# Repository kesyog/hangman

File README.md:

# hangman ⚖️

Hangman is a Bluetooth-enabled crane scale. It's intended use is as a climbing training and rehab
tool, but it can be used anywhere that requires measuring force or weight.

The hardware retrofits a cheap (~$23) 150kg crane scale from Amazon with a custom PCB based around a
Nordic nRF52 microcontroller and a differential ADC. The firmware uses [Embassy][Embassy], an
embedded async framework written in Rust, as well as Nordic's SoftDevice Bluetooth stack.

## Why?

Crane scales have become popular in the climbing community as a means to train and rehab fingers.
This is a fun project to learn and practice various concepts I was unfamiliar or rusty with: BLE
101, async Rust on embedded, nRF52 development, SMT soldering and PCB design, etc. Maybe it'll even
help my fingers get stronger.

## Status

The scale is feature-complete. Weight measurement works great with the [Progressor API][API] and
compatible tools. Battery life is guesstimated to be in the range of several months to a couple of
years depending on usage.

There are still a few more software updates planned. See the Issues section for the major ones.

### Hardware revisions

#### P1.0

See title picture. A custom PCB based on a Fanstel BT832 nRF52832-based module and a Texas
Instruments ADS1230 ADC. Thanks to a better ADC and PCB layout, noise performance should be improved
over previous revisions and most importantly, it's much prettier.

#### P0.0

A custom PCB based on a nRF52840 USB dongle and an HX711 ADC, the same differential ADC used on the
Tindeq.

## Shoutouts

* The [Embassy](https://embassy.dev) project for bringing asynchronous Rust to the embedded world.
  and creating an easy to use wrapper around the Nordic SoftDevice Bluetooth stack.
* [Bumble](https://github.com/google/bumble) for BLE testing and prototyping.
* Texas Instruments for their excellent reference materials on load cell circuit design and PCB
  layout.
* [Tindeq](https://tindeq.com/product/progressor/) for making an amazing product and app and opening
  their BLE API to third-party developers. Go buy one!

## Disclaimer

This is not an officially supported Google product. Wouldn't that be funny though?

This has no affiliation with Tindeq.

[API]: https://tindeq.com/progressor_api/
[Embassy]: https://embassy.dev/

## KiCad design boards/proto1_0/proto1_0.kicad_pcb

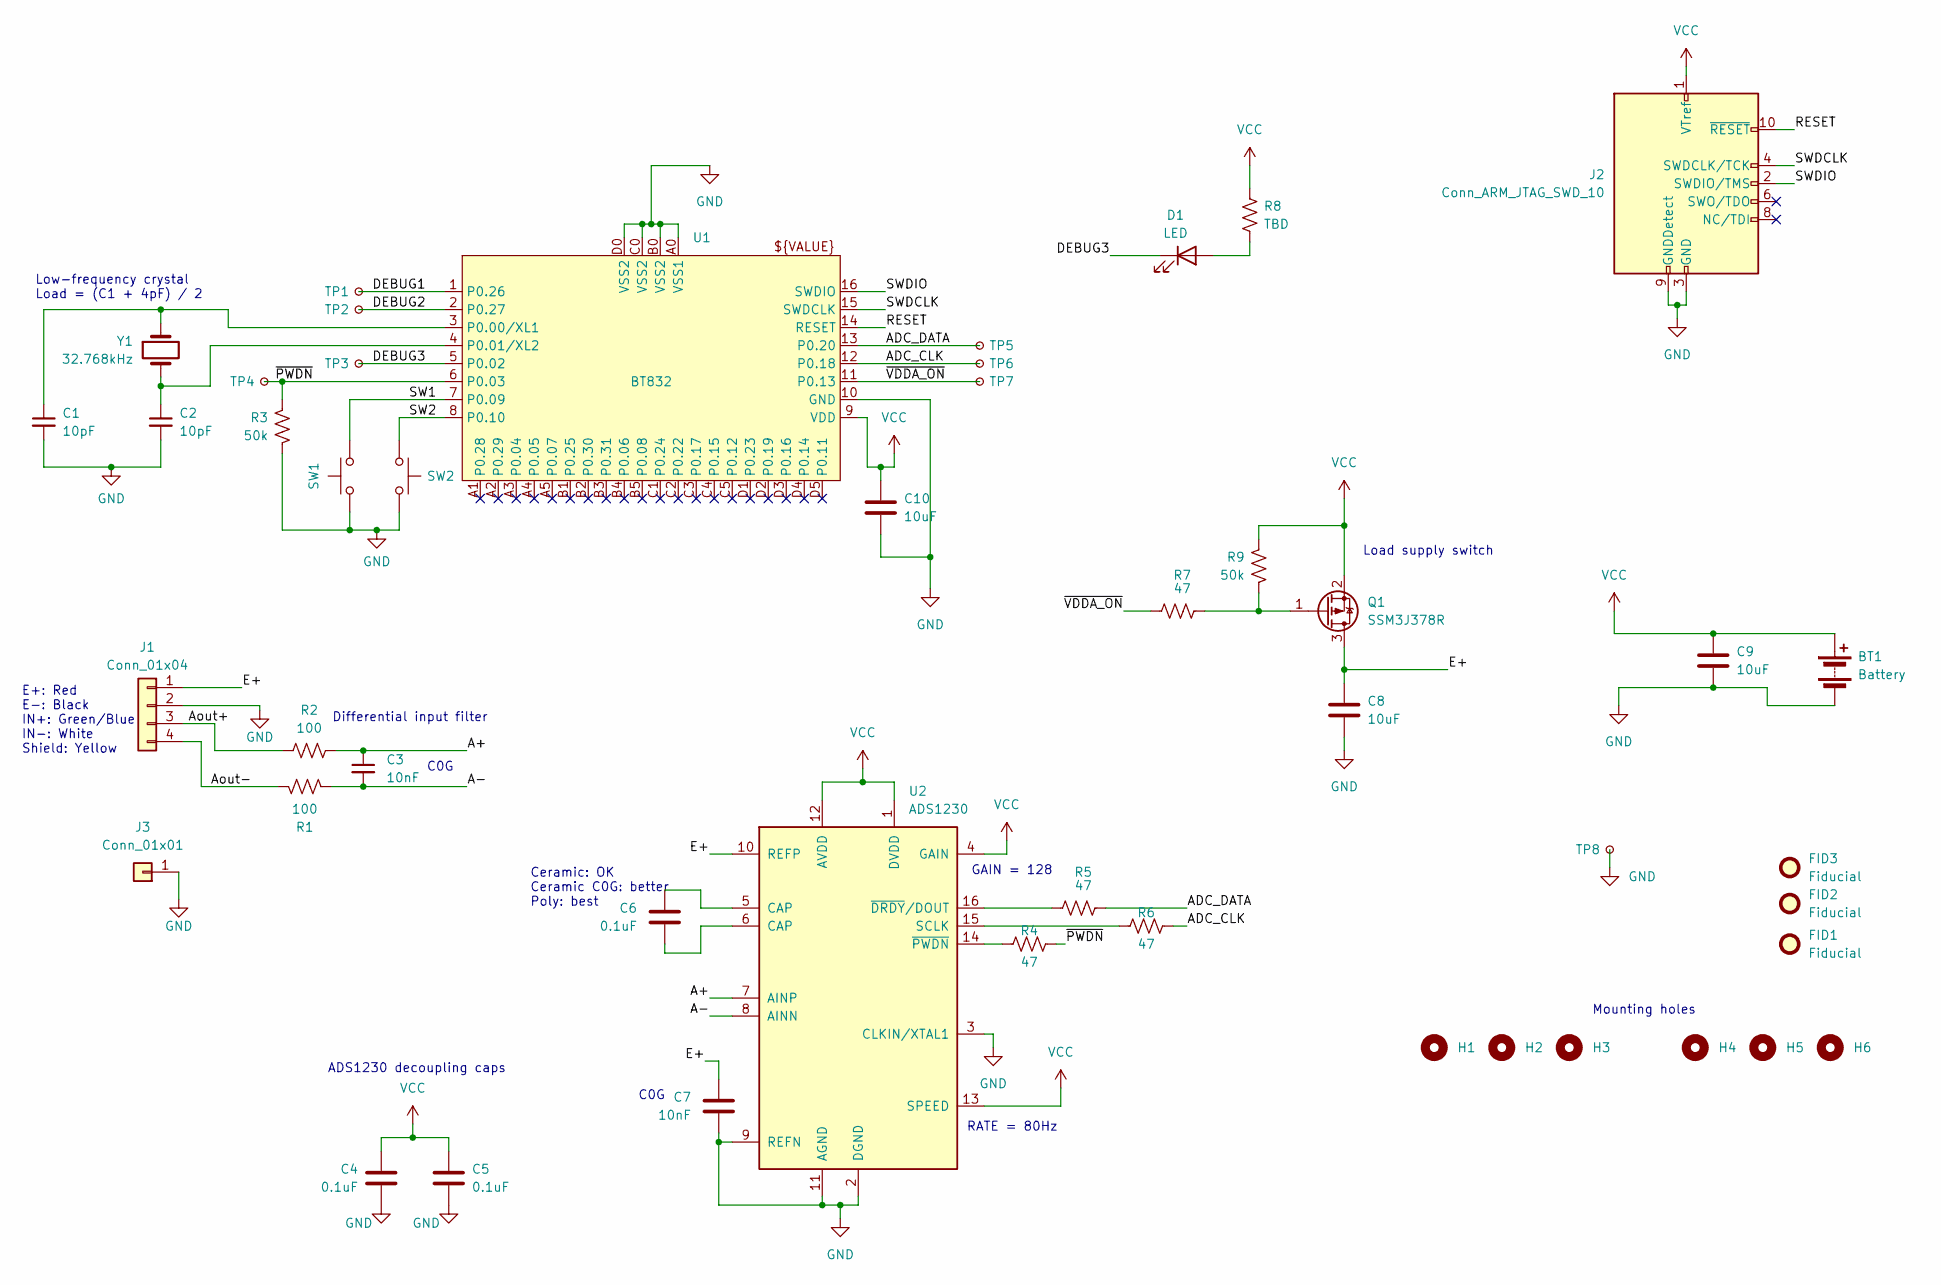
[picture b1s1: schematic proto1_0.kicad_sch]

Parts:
BT1: Battery; SolderWire-0.5sqmm_1x02_P4.6mm_D0.9mm_OD2.1mm
C1, C2: 10pF; C_0603_1608Metric
C3, C7: 10nF; C_0603_1608Metric
C4, C5, C6: 0.1uF; C_0603_1608Metric
C8, C9, C10: 10uF; C_0805_2012Metric
D1: LED; LED_0603_1608Metric_Pad1.05x0.95mm_HandSolder
FID1, FID2, FID3: Fiducial; Fiducial_0.5mm_Mask1mm
H1, H2, H3, H4, H5, H6: MountingHole; MountingHole_2.2mm_M2
J1: Conn_01x04; SolderWire-0.1sqmm_1x04_P3.6mm_D0.4mm_OD1mm
J2: Conn_ARM_JTAG_SWD_10; PinHeader_2x05_P1.27mm_Vertical_SMD
J3: Conn_01x01; SolderWire-0.5sqmm_1x01_D0.9mm_OD2.1mm
Q1: SSM3J378R; SOT-23
R1, R2: 100; R_0603_1608Metric
R3, R9: 50k; R_0603_1608Metric
R4, R5, R6, R7: 47; R_0603_1608Metric
R8: TBD; R_0805_2012Metric
SW1, SW2: 2223-TS02-66-70-BK-160-LCR-D-ND (Digikey); SW_PUSH_6mm_H7.3mm
TP1, TP2, TP3, TP4, TP5, TP6, TP7, TP8: TestPoint_Small; TestPoint_Pad_D1.5mm
U1: BT832
U2: ADS1230; TSSOP-16_4.4x5mm_P0.65mm
Y1: 32.768kHz; Crystal_SMD_3215-2Pin_3.2x1.5mm; Part number SC32S-7PF20PPM

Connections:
/A+: C3.1, R2.2, U2.7 (AINP)
/A-: C3.2, R1.2, U2.8 (AINN)
/ADC_CLK: R6.2, TP6.1, U1.12 (P0.18)
/ADC_DATA: R5.2, TP5.1, U1.13 (P0.20)
/Aout+: J1.3, R2.1
/Aout-: J1.4, R1.1
/DEBUG1: TP1.1, U1.1 (P0.26)
/DEBUG2: TP2.1, U1.2 (P0.27)
/DEBUG3: D1.1 (K), TP3.1, U1.5 (P0.02)
/E+: C7.1, C8.1, J1.1, Q1.3 (D), U2.10 (REFP)
/RESET: J2.10 (~RESET), U1.14 (RESET)
/SW1: SW1.1, U1.7 (P0.09)
/SW2: SW2.1, U1.8 (P0.10)
/SWDCLK: J2.4 (SWDCLK/TCK), U1.15 (SWDCLK)
/SWDIO: J2.2 (SWDIO/TMS), U1.16 (SWDIO)
/~PWDN: R3.1, R4.2, TP4.1, U1.6 (P0.03)
/~VDDA_ON: R7.1, TP7.1, U1.11 (P0.13)
GND: BT1.2 (-), C1.2, C2.2, C4.2, C5.2, C7.2, C8.2, C9.2, C10.2, J1.2, J2.3 (GND), J2.5 (GND), J2.9 (GNDDetect), J3.1, R3.2, SW1.2, SW2.2, TP8.1, U1.10 (GND), U1.A0 (VSS1), U1.B0 (VSS2), U1.C0 (VSS2), U1.D0 (VSS2), U2.2 (DGND), U2.3 (CLKIN/XTAL1), U2.9 (REFN), U2.11 (AGND)
unnamed: C6.1, U2.5 (CAP)
unnamed: C6.2, U2.6 (CAP)
unnamed: D1.2 (A), R8.2
unnamed: Q1.1 (G), R7.2, R9.2
unnamed: C1.1, U1.3 (P0.00/XL1), Y1.1
unnamed: C2.1, U1.4 (P0.01/XL2), Y1.2
unnamed: R6.1, U2.15 (SCLK)
unnamed: R5.1, U2.16 (~DRDY/DOUT)
unnamed: R4.1, U2.14 (~PWDN)
VCC: BT1.1 (+), C4.1, C5.1, C9.1, C10.1, J2.1 (VTref), Q1.2 (S), R8.1, R9.1, U1.9 (VDD), U2.1 (DVDD), U2.4 (GAIN), U2.12 (AVDD), U2.13 (SPEED)

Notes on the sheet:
Load supply switch
E+: Red E-: Black IN+: Green/Blue IN-: White Shield: Yellow
Differential input filter
Low-frequency crystal Load = (C1 + 4pF) / 2
C0G
Mounting holes
RATE = 80Hz
GAIN = 128
Ceramic: OK Ceramic C0G: better Poly: best
ADS1230 decoupling caps

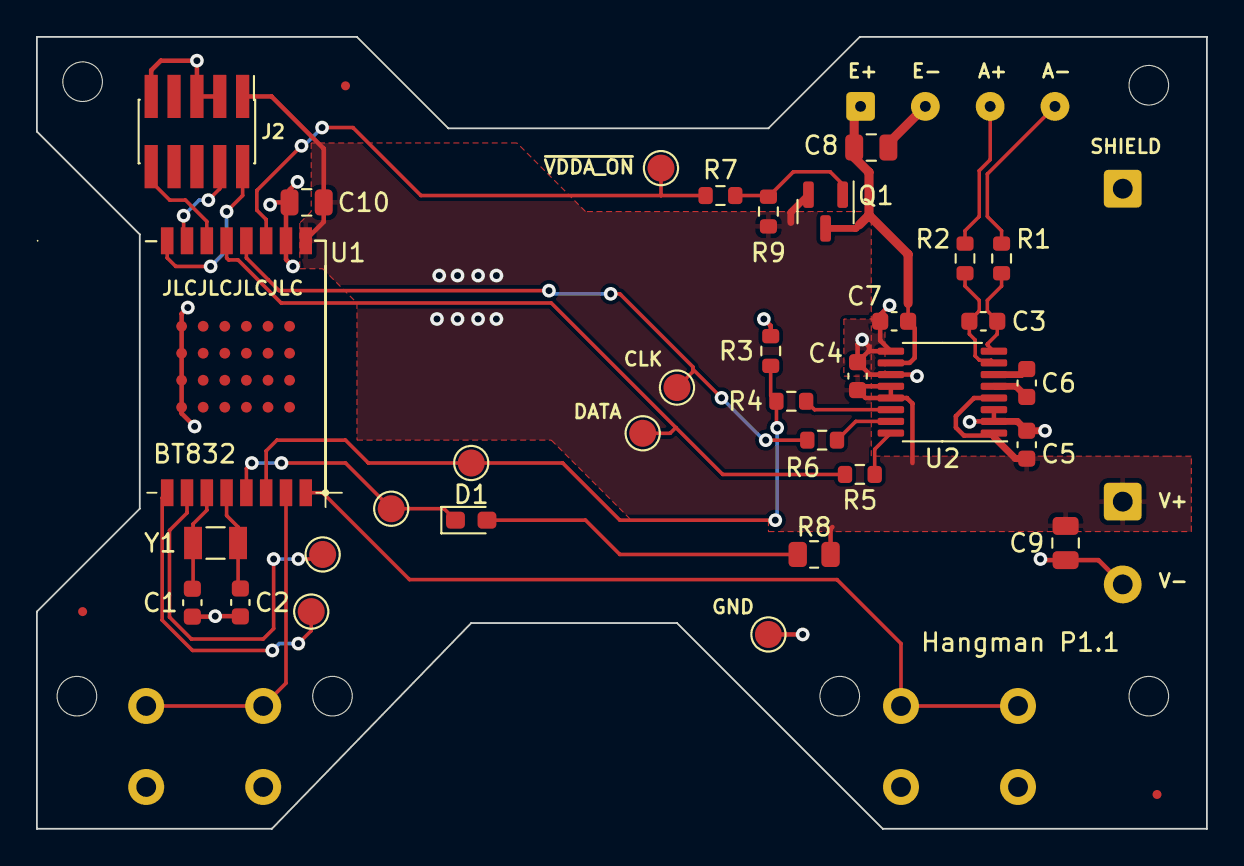
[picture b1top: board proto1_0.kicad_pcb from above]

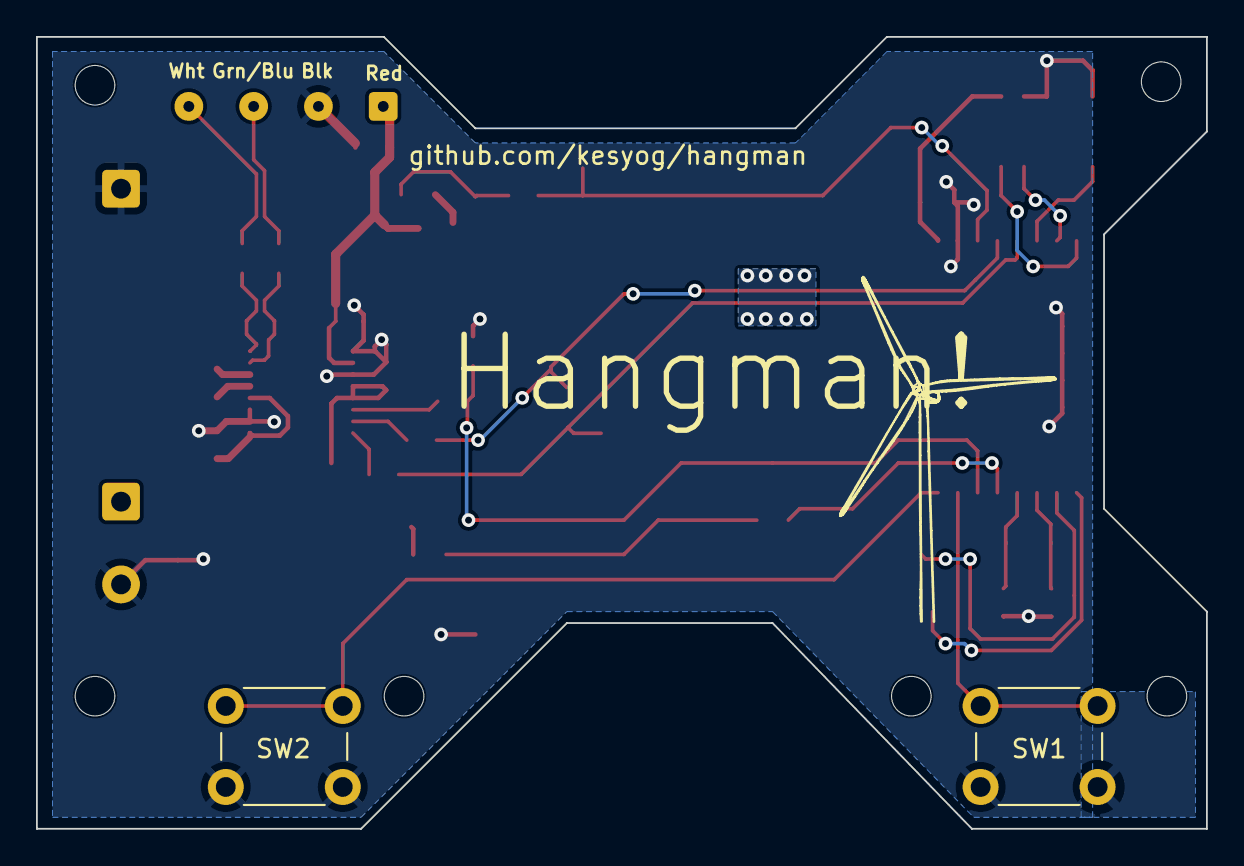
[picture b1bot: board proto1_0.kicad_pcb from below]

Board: 2 copper layers, 65.0 x 44.0 mm, 47 parts (2 on the bottom side), 28 nets.

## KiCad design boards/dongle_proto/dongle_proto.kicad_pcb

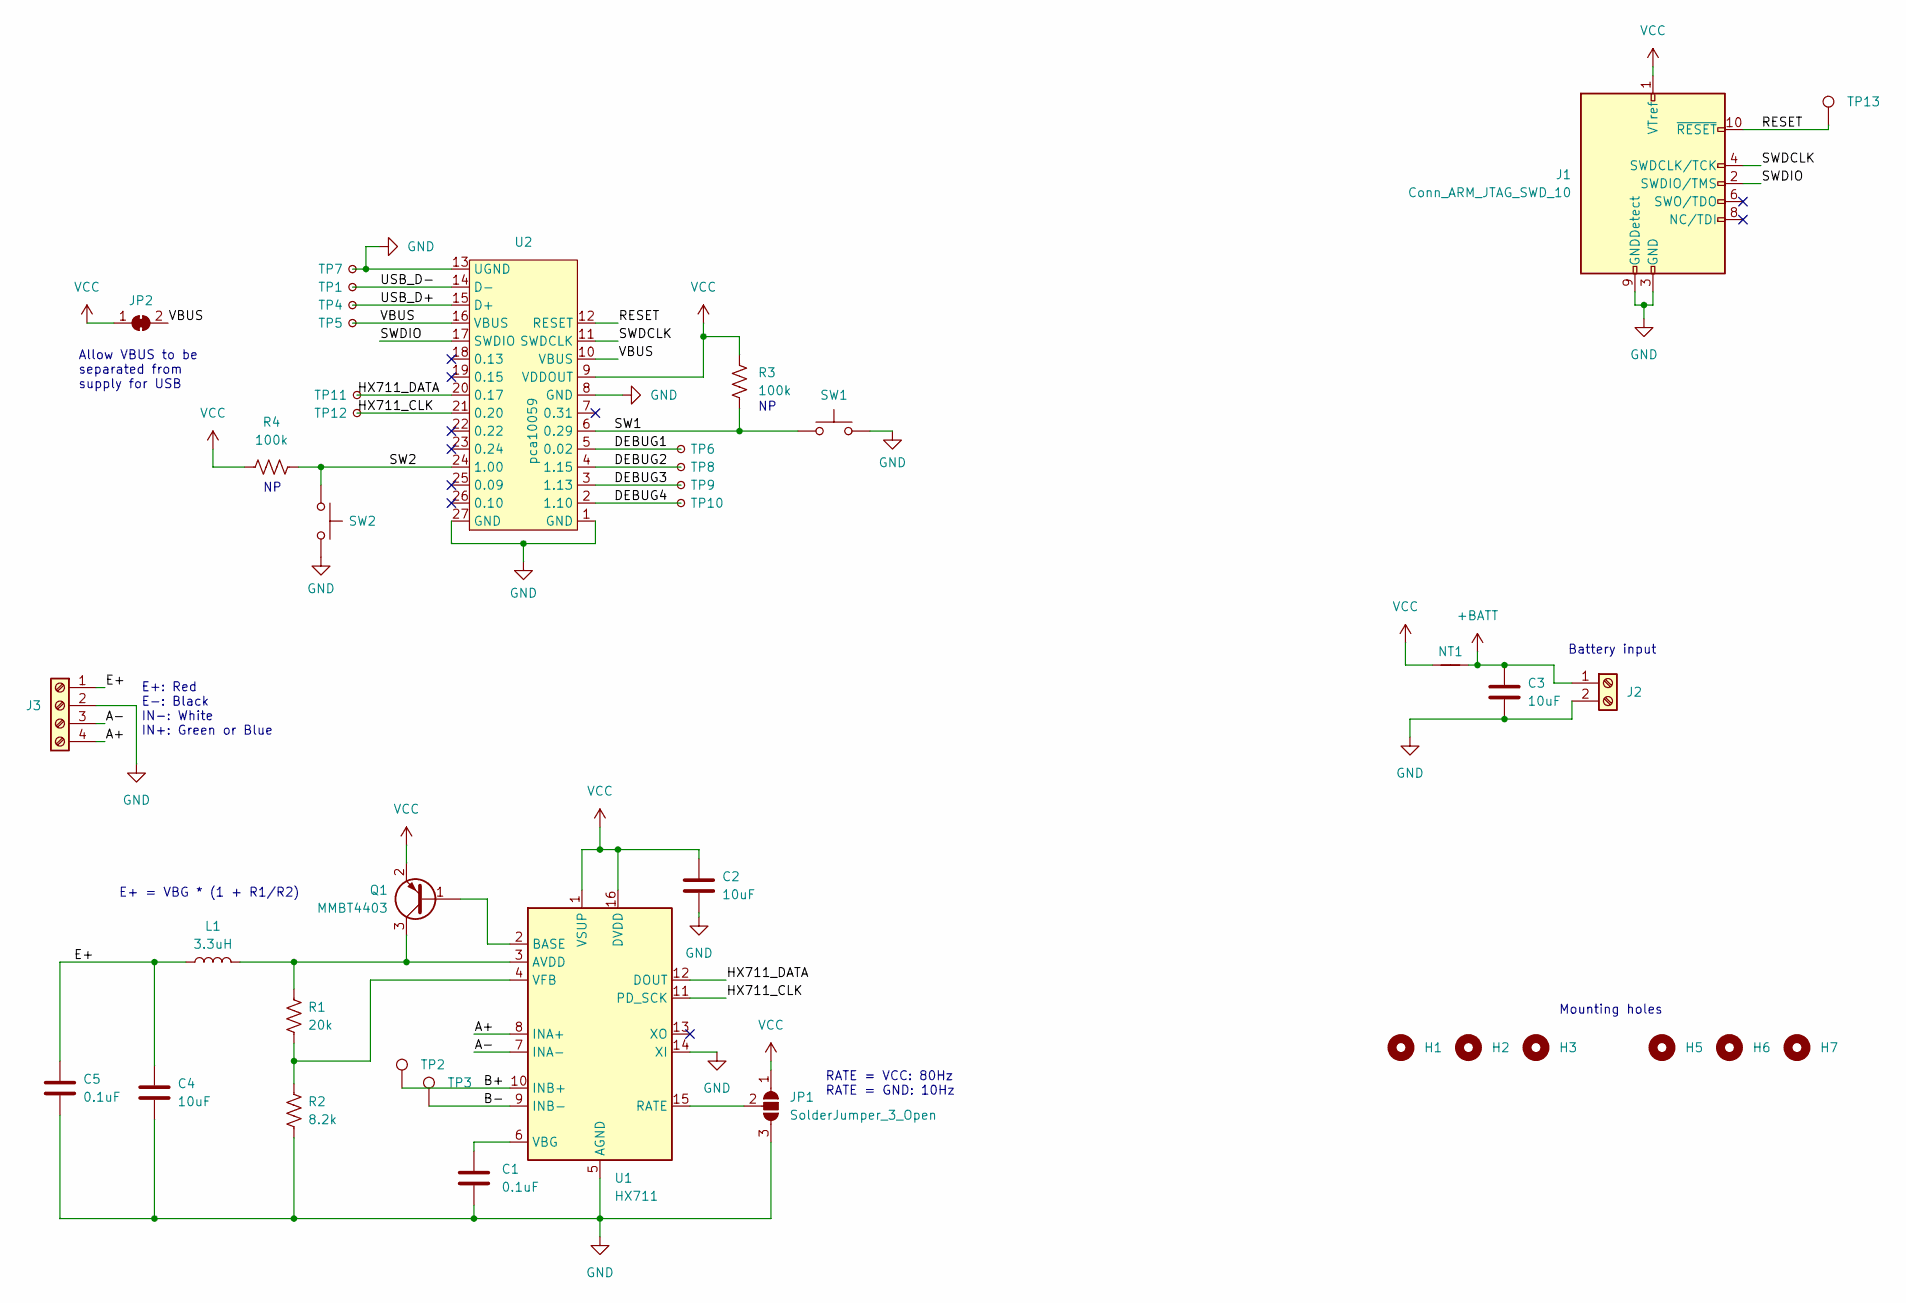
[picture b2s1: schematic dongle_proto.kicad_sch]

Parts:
C1, C5: 0.1uF; C_0805_2012Metric_Pad1.18x1.45mm_HandSolder
C2, C3, C4: 10uF; C_0805_2012Metric_Pad1.18x1.45mm_HandSolder
H1, H2, H3, H5, H6, H7: MountingHole; MountingHole_2.2mm_M2
J1: Conn_ARM_JTAG_SWD_10; PinHeader_2x05_P1.27mm_Vertical_SMD
J2: Screw_Terminal_01x02; TerminalBlock_Phoenix_MPT-0,5-2-2.54_1x02_P2.54mm_Horizontal
J3: Screw_Terminal_01x04; TerminalBlock_Phoenix_MPT-0,5-4-2.54_1x04_P2.54mm_Horizontal
JP1: SolderJumper_3_Open; SolderJumper-3_P1.3mm_Open_RoundedPad1.0x1.5mm
JP2: SolderJumper_2_Bridged; SolderJumper-2_P1.3mm_Bridged_RoundedPad1.0x1.5mm
L1: 3.3uH; L_0805_2012Metric_Pad1.05x1.20mm_HandSolder
NT1: NetTie_2; NetTie-2_SMD_Pad2.0mm
Q1: MMBT4403; SOT-23_Handsoldering
R1: 20k; R_0805_2012Metric_Pad1.20x1.40mm_HandSolder
R2: 8.2k; R_0805_2012Metric_Pad1.20x1.40mm_HandSolder
R3, R4: 100k; R_0805_2012Metric_Pad1.20x1.40mm_HandSolder
SW1, SW2: 2223-TS02-66-70-BK-160-LCR-D-ND (Digikey); SW_PUSH_6mm_H7.3mm
TP1, TP4, TP5, TP6, TP7, TP8, TP9, TP10, TP11, TP12: TestPoint_Small; TestPoint_Pad_D1.5mm
TP2, TP3, TP13: TestPoint; TestPoint_Pad_D1.5mm
U1: HX711; SOP-16_3.9x9.9mm_P1.27mm
U2: pca10059

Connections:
+BATT: C3.1, J2.1, NT1.2
/A+: J3.4, U1.8 (INA+)
/A-: J3.3, U1.7 (INA-)
/B+: TP2.1, U1.10 (INB+)
/B-: TP3.1, U1.9 (INB-)
/DEBUG1: TP6.1, U2.5 (0.02)
/DEBUG2: TP8.1, U2.4 (1.15)
/DEBUG3: TP9.1, U2.3 (1.13)
/DEBUG4: TP10.1, U2.2 (1.10)
/E+: C4.1, C5.1, J3.1, L1.1
/HX711_CLK: TP12.1, U1.11 (PD_SCK), U2.21 (0.20)
/HX711_DATA: TP11.1, U1.12 (DOUT), U2.20 (0.17)
/RESET: J1.10 (~RESET), TP13.1, U2.12 (RESET)
/SW1: R3.2, SW1.1, U2.6 (0.29)
/SW2: R4.2, SW2.1, U2.24 (1.00)
/SWDCLK: J1.4 (SWDCLK/TCK), U2.11 (SWDCLK)
/SWDIO: J1.2 (SWDIO/TMS), U2.17 (SWDIO)
/USB_D+: TP4.1, U2.15 (D+)
/USB_D-: TP1.1, U2.14 (D-)
/VBUS: JP2.2 (B), TP5.1, U2.10 (VBUS), U2.16 (VBUS)
GND: C1.2, C2.2, C3.2, C4.2, C5.2, J1.3 (GND), J1.5 (GND), J1.9 (GNDDetect), J2.2, J3.2, JP1.3 (B), R2.2, SW1.2, SW2.2, TP7.1, U1.5 (AGND), U1.14 (XI), U2.1 (GND), U2.8 (GND), U2.13 (UGND), U2.27 (GND)
unnamed: JP1.2 (C), U1.15 (RATE)
unnamed: Q1.1 (B), U1.2 (BASE)
unnamed: L1.2, Q1.3 (C), R1.1, U1.3 (AVDD)
unnamed: C1.1, U1.6 (VBG)
unnamed: R1.2, R2.1, U1.4 (VFB)
VCC: C2.1, J1.1 (VTref), JP1.1 (A), JP2.1 (A), NT1.1, Q1.2 (E), R3.1, R4.1, U1.1 (VSUP), U1.16 (DVDD), U2.9 (VDDOUT)

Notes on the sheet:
Battery input
E+: Red E-: Black IN-: White IN+: Green or Blue
Mounting holes
E+ = VBG * (1 + R1/R2)
Allow VBUS to be separated from supply for USB
RATE = VCC: 80Hz RATE = GND: 10Hz

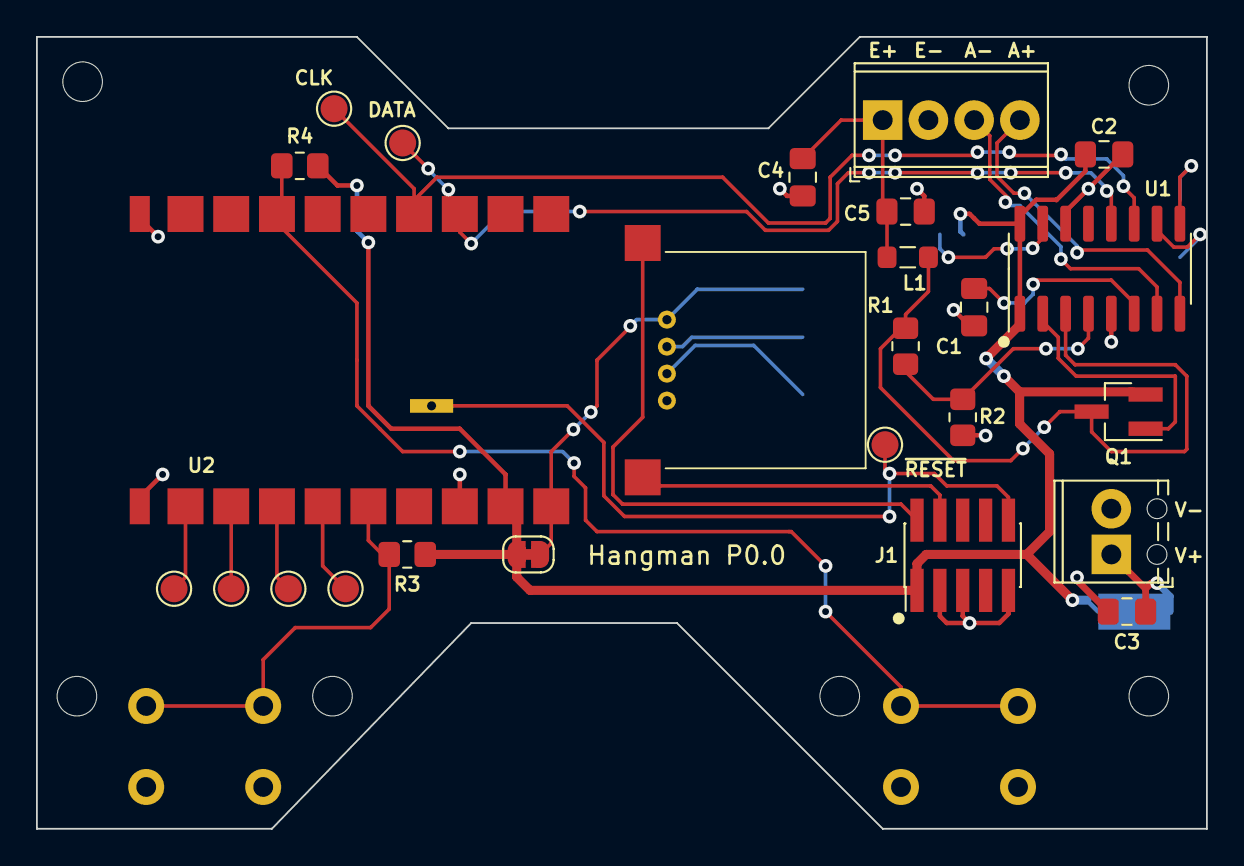
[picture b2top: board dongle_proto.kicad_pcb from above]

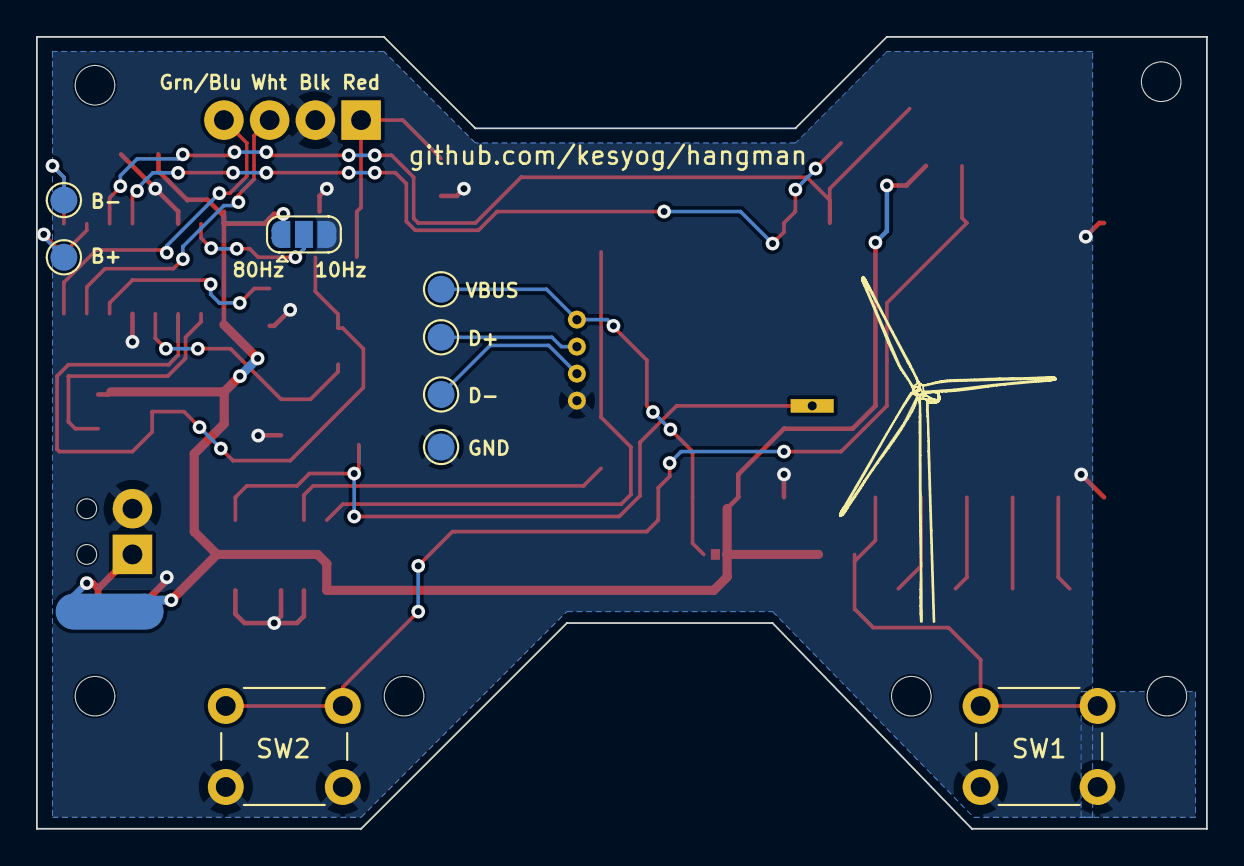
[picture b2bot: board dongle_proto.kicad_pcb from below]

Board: 2 copper layers, 65.0 x 44.0 mm, 40 parts (10 on the bottom side), 27 nets.

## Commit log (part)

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2023-02-05 Working blinky on nRF52840 dongle
2023-02-05 Switch to Embassy executor and HAL
    Using the async Embassy framework will be required to use the
    `nrf-softdevice` crate, which we'll likely later use to access the
    SoftDevice.
2023-02-05 Use nrfutil to load FW via the Nordic bootloader
    Nordic's GUI programming tool doesn't work well with the bootloader
2023-02-11 Add CDC-ACM USB class with echo
2023-02-11 Add logging over RTT
    * Add support for defmt logging over RTT
    * Switch cargo runner to probe-run, which supports defmt parsing
2023-02-11 Start the SoftDevice
2023-02-20 Add measurement task with fake data
2023-02-26 Add small heap for passing around closures
2023-02-26 Add NVM driver to store calibration constants
    Bonus: lower most `println` logs to lower priorities
2023-02-26 Hook up HX711 driver to GATT commands
    * Add bit-banged HX711 driver
    * Add some default calibration constants
    * Show status with LED's
    * Reduce RAM section size to simulate smallest nRF52 chip
    It works with the Tindeq app!
2023-02-27 Remove measurement -> gatt notify dependency via callback
2023-07-15 Fix breaking changes in dependencies
    embassy made a lot of breaking changes in their git repo. Their API's
    are not stable and the dependency is not pinned to any specific git
    commit.
    Fix up the breaking changes and update all dependencies while we're at
    it.
2023-07-15 Add additional control event opcodes
    Add definitions and parsing of additional undocumented control point
    opcodes. For now, these opcodes are logged but otherwise ignored.
2023-07-16 Make reported sample timestamps more accurate
    Treat the moment that the HX711 reports a sample is ready as the sample
    time. We were previously reading a timestamp after the sample had been
    shifted out to the processor, which introduces a relatively fixed offset
    that shouldn't matter in practice, but accuracy is accuracy.
2023-07-25 🤞🏽 Add Kicad files for P0.0 prototype board
    Add schematic, symbol library, footprint library, and layout for P0.0
    prototype board.
2023-07-29 Simplify/complicate window averager via generics
2023-07-29 🧹 Refactor weight sampling code
    Goals:
    * Make it easier to add new functionality, especially filtering (for
    calibration and taring) and a calibration flow.
    * Clean up a lot of cruft that made things extra hard to follow and
    edit.
    Changes:
2023-07-29 Fix crash in Flash driver
    Flash transactions must only be performed with 4-byte aligned buffers
2023-07-29 Simplify NVM API and remove strum dependency
2023-07-29 Disable USB by default
    * Move as much USB code out of main.rs as possible.
    * Gate USB and echo task on the "console" feature, which is disabled by
    default.
2023-07-29 Reduce logging level of individual measurements
2023-08-04 Use window filter when taring scale
2023-08-17 Fix HX711 AVDD level
    The HX711's analog output (AVDD) should be set below its supply voltage
    (the battery voltage) so that the chip's feedback loop can create a
    stable excitation voltage that is resilient to load transients. The
    R1/R2 resistor ladder was set such that AVDD would always rail to the
    supply voltage. Set it to ~2.7-2.8V instead.
    Note: it's possible that this doesn't actually matter since the ADC
2023-08-17 Reduce sample noise + miscellaneous cleanup
    * Add 5-point median filter in sample pipeline to filter glitches in
    samples
    * Use `make_static!` convenience macro to initialize `StaticCell`s
    * Disable LED's to save power
    * Store window size in window average rather than using const generics
    to reduce monomorphization code bloat.
2023-08-20 Fix Clippy lints
2023-08-21 Create separate binary for manual calibration
    Stuffing everything into one binary was becoming increasingly painful.
    Create a lib crate and separate binaries for the main scale code and the
    manual calibration code.
    Eventually, we'll likely want separate binaries for each board variant
    and and to think harder about how to move common code into the lib
    crate. Ideally, the code in the binaries will be entirely
2023-08-21 Return dummy responses to speed up connection
    The Tindeq app queries a few parameters on connection and also when the
    settings page is opened in the app:
    * Versino number
    * Battery voltage
    * Progressor ID (undocumented query with opcode 0x70)
    These requests were being ignored. Although the app eventually gives up
2023-08-25 Enter system OFF between BLE connections to save power
    * Enter system OFF after advertising timeouts or disconnects, using the
    wakeup button as the wakeup trigger.
    * Minor cleanup: centralize the definition of the `blocking_hal` and pac
    crates to make it easier to switch to other nRF52 parts in the future.
2023-08-26 Enable DC-DC converter for power savings
    The MCU should automatically switch between the DC-DC converter and the
    LDO to optimize conversion efficiency. Didn't actually measure power
    with and without this change but it _should_ work 😬
2023-08-26 Inject sampling frequency from binary
    The dongle development setup is configured with a 10Hz sampling
    frequency, whereas everything else uses 80Hz. Allow this parameter to be
    injected into the weight task rather than hard-coding it.
    The sampling frequency is primarily used for configuring the taring
    process. Accidentally using the default 80Hz value with the dongle
    results in very slow startup.
2023-08-26 Reduce SoftDevice RAM usage via easy-mode tuning
    * Reduce SoftDevice RAM memory usage from ~15kB to ~8kB, knowing that we
    only support one connection at a time and should only need a small
    MTU. This gives even more headroom to use smaller nRF52 devices, if
    desired, which only have 24kB of RAM.
    * Allow 2M secondary Phy. This might save some marginal power by running
    the radio less.
2023-08-29 Add proto1_0 board
    Add schematic and PCB for another prototype board, P1.0.
    Main changes from the first prototype PCB (P0.0):
    * Based on TI ADS1230 ADC IC rather than HX711
    * More thoughtful layout of ADC
    * Using Fanstel BT832 module rather than a Nordic USB dongle
    This will require some software changes to get working in a future
2023-09-10 Fix bad transistor pin assignment
    The load cell power switch (Q1) used a PFET symbol that incorrectly
    numbered its pins relative to the industry-standard for SOT-23 packages.
    Use a more accurate symbol instead and fix the layout accordingly.
    While a P1.1 board is not (yet) planned since this issue should be easy
    to work around,, I've kept the footprint locations the same so that the
    P1.0 stencil can be reused.
2023-09-25 Support runtime calibration via Bluetooth
    Add two-point calibration over Bluetooth. To simplify the math required,
    one of the points must be zero.
    The routine uses documented calibration opcodes but uses its own payload
    format:
    Add calibration point:
    Opcode: 0x69
2023-09-25 Ensure checksum write to flash is aligned
    Writes to flash must originate from 4-byte buffers. This wasn't being
    enforced, so we were getting lucky.
2023-09-25 Fix flipped PCB silkscreen
    The white and green color labels for the load cell differential output
    voltage pins were switched. There's no real functional effect since the
    negative polarity would be fixed in calibration, but one can swap the
    wires if desired.
2023-09-25 Add support for Proto 1.0 board
    * Add mutually-exclusive feature flags for nRF52832 and nRF52840. This
    abuses the feature flag system, but that's embedded life for you.
    Embassy also uses this pattern.
    * Add ADS1230 driver
    * Add blinky, calibration, and application binaries for Proto 1.0
    Note: Some library code abuses the nRF52832 vs. nRF52840 feature flags
2023-09-25 Add missing license headers
2023-10-01 Enable excitation voltage only when needed 🔋
    Save some power by only enabling the load cell excitation voltage when
    actively measuring. This should save (~10-35mW) when Hangman is awake
    but not actively measuring.
2023-10-01 Sample battery voltage at startup
    * Sample battery voltage at startup
    * Shut down immediately if critically low (<= 2.7V)
    * Report low battery warning and disconnect from connected peer if
    battery is just low (<= 2.75V)
2023-10-01 Cleanup some Clippy lints and add documentation
    Also add some basic state checking to weight command handler
2023-10-01 Reduce BLE transmit power from 0dB to -4dB
    This saves some amount of power while still providing plenty of range
    (at least 10 feet through walls). Not going to reduce further because it
    has diminishing returns.
2023-10-01 Random cleanup 🧹
    * Remove obsolete leds module
    * Use `RawReading` type in more places
    * Fix a Clippy lint
2023-10-02 Use a single source of truth for device name
    The device name used for GAP and advertising was defined in two places.
    Define a single source of truth so that its easier to change.
2023-10-02 Add defmt type hints
2023-10-02 Remove unnecessary GATT types and conversion code
    * Remove `from_gatt` implementation for outgoing types and `to_gatt`
    implementation for incoming types, as these functions are never
    called.
    * Remove intermediate control point type. There is no need for a
    byte-equivalent type since we do not need a `to_gatt` implementation.
2023-10-03 Add mdbook and calibration instructions
2023-10-03 Fix broken mdbook link
2023-10-04 Fix advertised device name
    The advertising data was missing the
    `BLE_GAP_AD_TYPE_COMPLETE_LOCAL_NAME` flag, leading it to show up as a
    blank device name in the Tindeq app.
2023-10-07 Remove nagging error message at connection time
    * Provide response to get calibration curve control message. The default
    value can be overridden at compile time via the `CALIBRATION_CURVE`
    environment variable.
    * Add support for device ids up to 8 bytes
2023-10-09 Fix typos caught by Mark and Chris
2023-10-13 Use probe-rs as cargo runner
    probe-run is deprecated in favor of probe-rs. See
    https://ferrous-systems.com/blog/probe-run-deprecation
2023-10-13 Update dependencies and fix new warnings
    Notable changes
    * Updating Embassy was, as usual, a minor pain.
    * Embassy requires a more recent of the nightly compiler.
    * There was a breaking API change to a embassy_sync channel API, but
    luckily it was just a name change.
    * The compiler advised against using async functions in public traits.
2024-01-23 Pull Embassy crates from crates.io 🎉
    Embassy published their crates to crates.io so we no longer need to add
    them as git dependencies. This should remove the previously-encountered
    pain of breaking API changes suddenly breaking things.
    Also remove the `async_fn_in_trait` nightly feature flag now that it's
    on stable.
2024-06-01 Split out utility crate for host unit testing
    Split source code into a hangman crate and a hangman_utils crate. This
    allows for easy host unit testing of the utilities.
2024-06-01 Add CI via GitHub Actions
2024-07-06 Ignore target folder in subdirectories
2024-07-06 Re-implement broken make_static! macro
    static-cell's `make_static!` macro is broken in latest nightly:
    https://github.com/embassy-rs/static-cell/issues/16
    Re-implement it by dropping the automatic type deduction magic.
2024-07-06 Add Rust Analyzer configurations
    Add Rust Analyzer configurations for Neovim and VS Code. This silences
    some annoying false positive diagnostics.
    Using the neovim configuration requires
    [folke/neoconf.nvim](https://github.com/folke/neoconf.nvim).
2025-09-04 Fix mdbook GitHub Action
    Rev actions versions to avoid using deprecated actions
2025-09-22 Improve and correct documentation
2025-11-14 Update flashing instructions
2025-11-16 Fix mdbook configuration
    Remove invalid multilingual key
